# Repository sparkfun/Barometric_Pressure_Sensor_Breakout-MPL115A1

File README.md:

SparkFun Barometric Pressure Sensor Breakout - MPL115A1
========================================

[*SparkFun Barometric Pressure Sensor Breakout - MPL115A1 (SEN-09721)*](https://www.sparkfun.com/products/9721)

Now mounted on a breakout board, the MPL115A1 is a digital barometer that uses MEMs technology to give accurate pressure measurements between 50kPa and 115kPa.
We stock the SPI interface version of the sensor. 
Average current consumption is 10µA at one measurement per second.

Repository Contents
-------------------

* **/Firmware** - Example code 
* **/Hardware** - Eagle design files (.brd, .sch)
* **/Libraries** - Libraries for use with the <PRODUCT NAME>
* **/Production** - Production panel files (.brd)

Documentation
--------------
* **[SparkFun Fritzing repo](https://github.com/sparkfun/Fritzing_Parts)** - Fritzing diagrams for SparkFun products.
* **[SparkFun 3D Model repo](https://github.com/sparkfun/3D_Models)** - 3D models of SparkFun products. 

License Information
-------------------
This product is _**open source**_! 

The **hardware** is released under [Creative Commons ShareAlike 4.0 International](https://creativecommons.org/licenses/by-sa/4.0/).

The **code** is beerware; if you see me (or any other SparkFun employee) at the local, and you've found our code helpful, please buy us a round!

Please use, reuse, and modify these files as you see fit. Please maintain attribution to SparkFun Electronics and release anything derivative under the same license.

Distributed as-is; no warranty is given.

- Your friends at SparkFun.

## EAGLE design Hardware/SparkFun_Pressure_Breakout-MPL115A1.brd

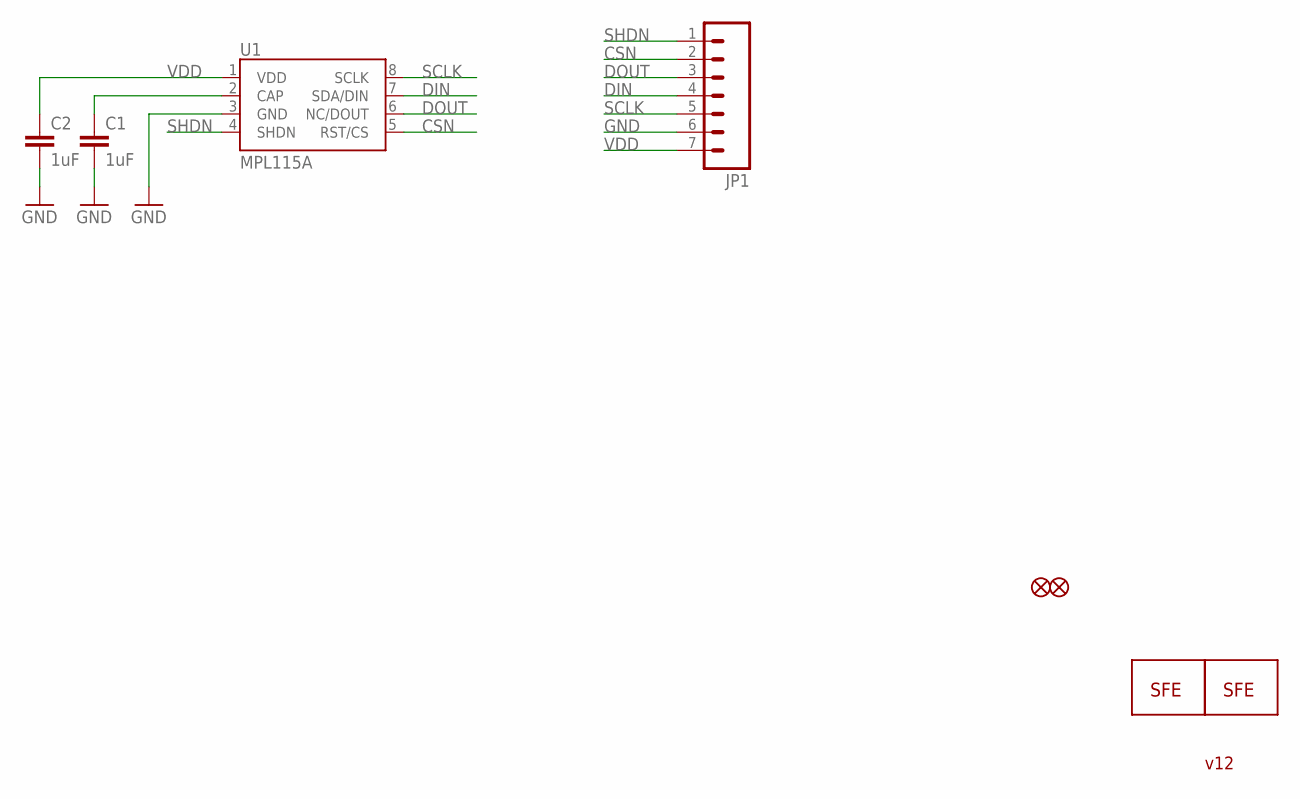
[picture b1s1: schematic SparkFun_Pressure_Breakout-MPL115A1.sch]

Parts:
C1, C2: 1uF; 0603-CAP
FID1, FID2: FIDUCIALUFIDUCIAL; MICRO-FIDUCIAL
JP1: M07; 1X07
JP2: LOGO-SFESK; SFE-LOGO-FLAME
JP3: LOGO-SFENW2; SFE-NEW-WEB
U1: MPL115A; LGA8

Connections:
CAP: C1.1, U1.2 (CAP)
CSN: JP1.2, U1.5 (RST/CS)
DIN: JP1.4, U1.7 (SDA/DIN)
DOUT: JP1.3, U1.6 (NC/DOUT)
GND: C1.2, C2.2, JP1.6, U1.3 (GND)
SCLK: JP1.5, U1.8 (SCLK)
SHDN: JP1.1, U1.4 (SHDN)
VDD: C2.1, JP1.7, U1.1 (VDD)

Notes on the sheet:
v12

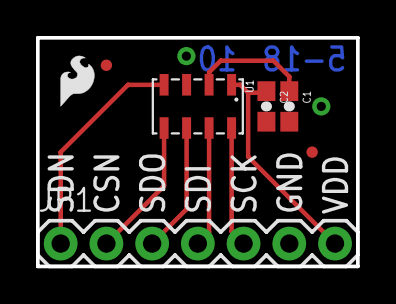
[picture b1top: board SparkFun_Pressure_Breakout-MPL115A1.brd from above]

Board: 2 copper layers, 17.8 x 12.7 mm, 8 parts (1 on the bottom side), 8 nets.

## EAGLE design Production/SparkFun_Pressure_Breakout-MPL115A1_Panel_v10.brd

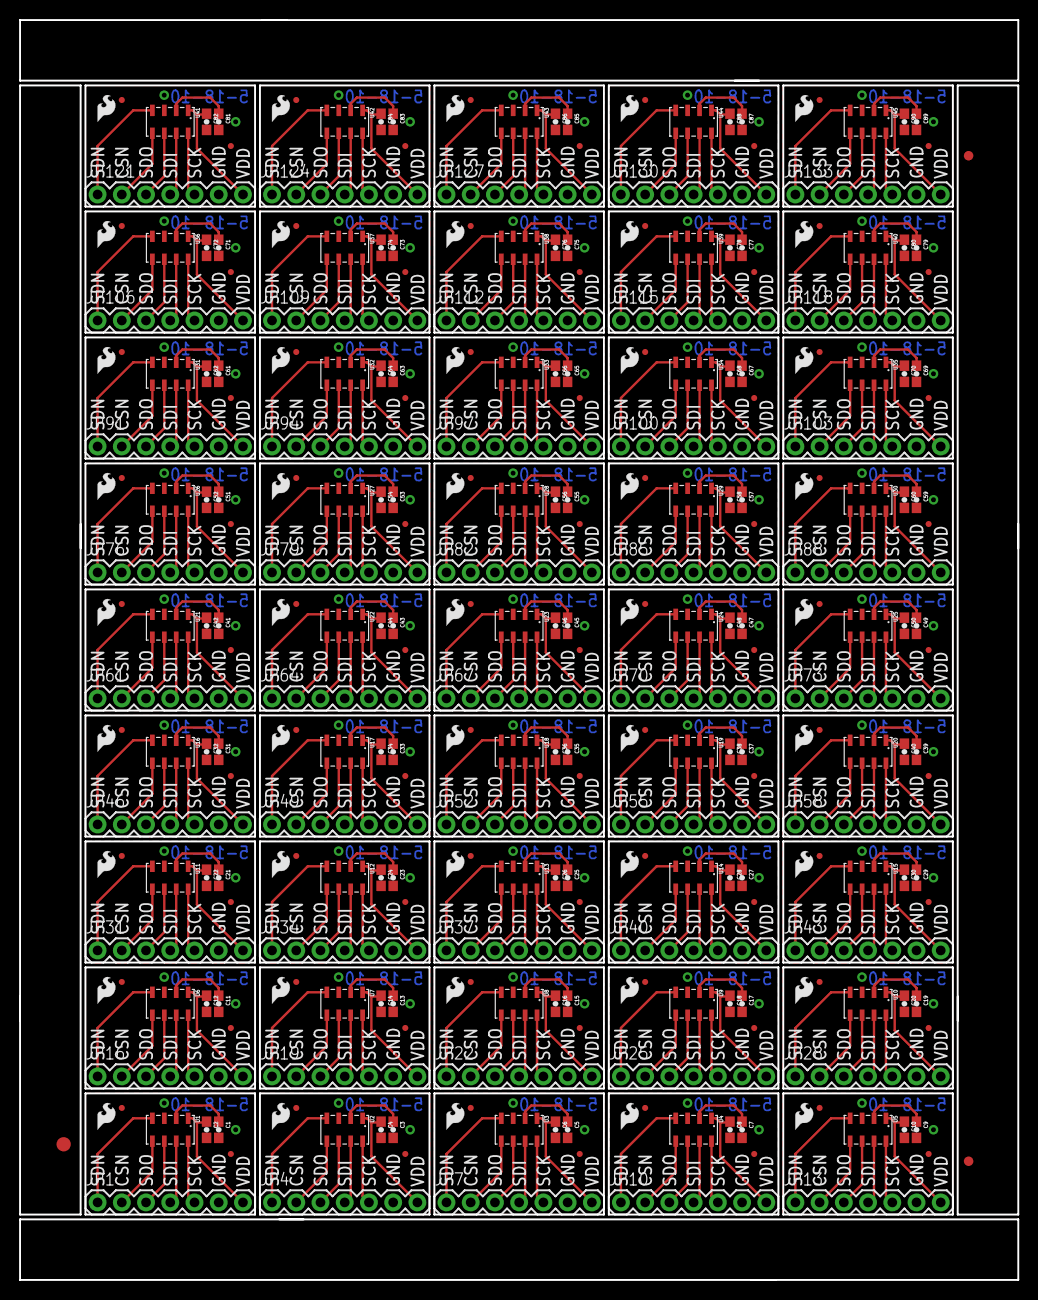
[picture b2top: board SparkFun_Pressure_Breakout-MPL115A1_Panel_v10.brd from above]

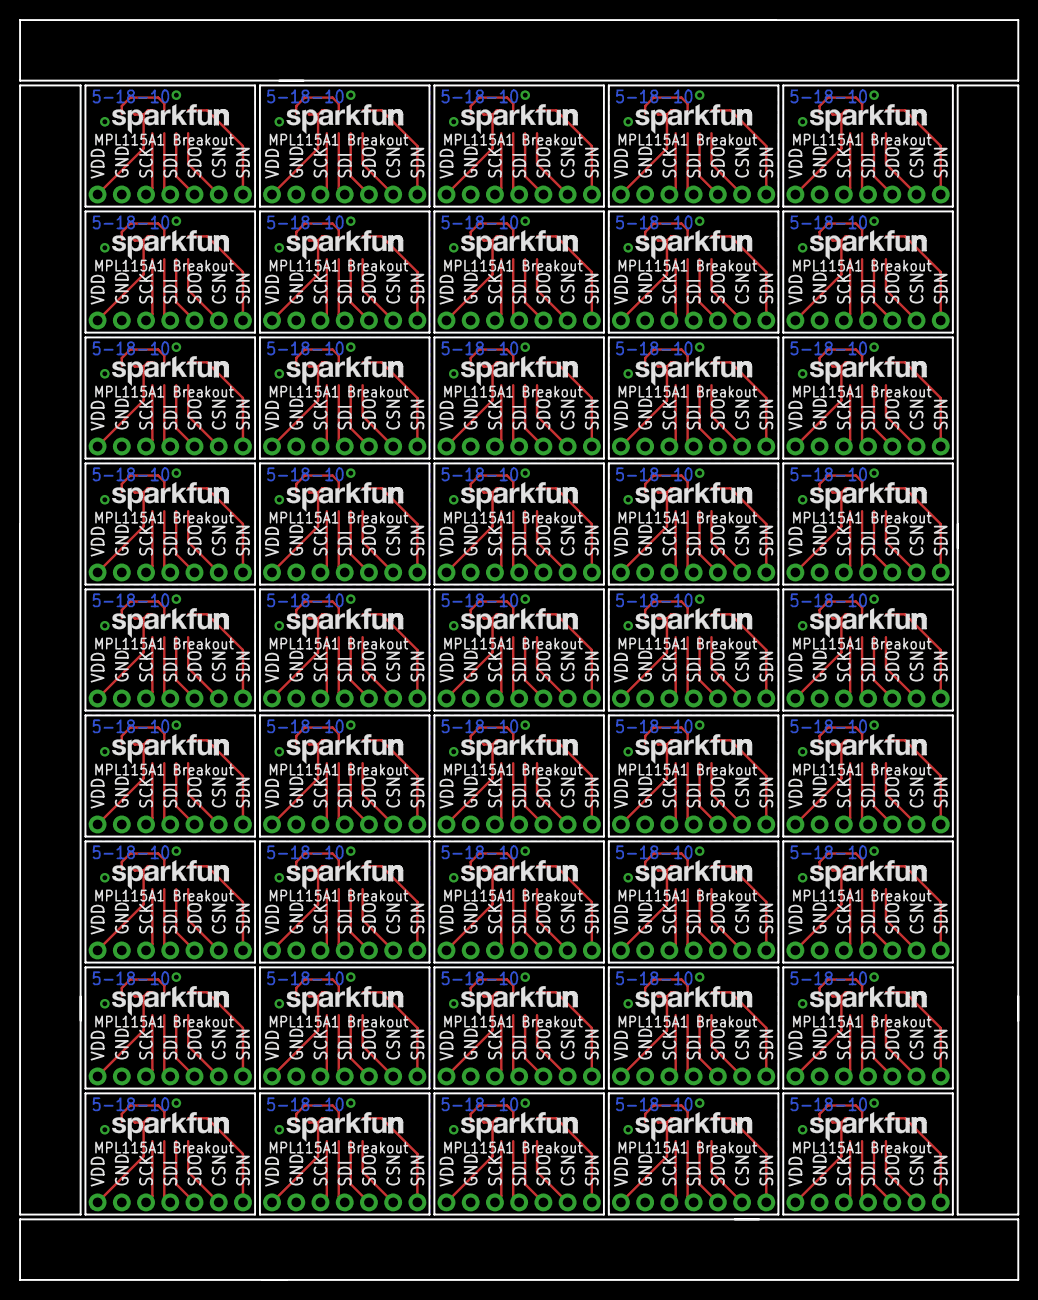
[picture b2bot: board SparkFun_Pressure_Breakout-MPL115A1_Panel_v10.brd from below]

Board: 2 copper layers, 104.6 x 132.1 mm, 363 parts (45 on the bottom side), 360 nets.

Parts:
C1, C2, C3, C4, C5, C6, C7, C8, C9, C10, C11, C12, C13, C14, C15, C16, C17, C18, C19, C20, C21, C22, C23, C24, C25, C26, C27, C28, C29, C30, C31, C32, C33, C34, C35, C36, C37, C38, C39, C40, C41, C42, C43, C44, C45, C46, C47, C48, C49, C50, C51, C52, C53, C54, C55, C56, C57, C58, C59, C60, C61, C62, C63, C64, C65, C66, C67, C68, C69, C70, C71, C72, C73, C74, C75, C76, C77, C78, C79, C80, C81, C82, C83, C84, C85, C86, C87, C88, C89, C90: 1uF; 0603-CAP
E$1: FIDUCIAL-1.5X3
E$5, E$6: FIDUCIAL-1X2
FID1, FID2, FID3, FID4, FID5, FID6, FID7, FID8, FID9, FID10, FID11, FID12, FID13, FID14, FID15, FID16, FID17, FID18, FID19, FID20, FID21, FID22, FID23, FID24, FID25, FID26, FID27, FID28, FID29, FID30, FID31, FID32, FID33, FID34, FID35, FID36, FID37, FID38, FID39, FID40, FID41, FID42, FID43, FID44, FID45, FID46, FID47, FID48, FID49, FID50, FID51, FID52, FID53, FID54, FID55, FID56, FID57, FID58, FID59, FID60, FID61, FID62, FID63, FID64, FID65, FID66, FID67, FID68, FID69, FID70, FID71, FID72, FID73, FID74, FID75, FID76, FID77, FID78, FID79, FID80, FID81, FID82, FID83, FID84, FID85, FID86, FID87, FID88, FID89, FID90: FIDUCIALUFIDUCIAL; MICRO-FIDUCIAL
JP1, JP4, JP7, JP10, JP13, JP16, JP19, JP22, JP25, JP28, JP31, JP34, JP37, JP40, JP43, JP46, JP49, JP52, JP55, JP58, JP61, JP64, JP67, JP70, JP73, JP76, JP79, JP82, JP85, JP88, JP91, JP94, JP97, JP100, JP103, JP106, JP109, JP112, JP115, JP118, JP121, JP124, JP127, JP130, JP133: 1X07
JP2, JP5, JP8, JP11, JP14, JP17, JP20, JP23, JP26, JP29, JP32, JP35, JP38, JP41, JP44, JP47, JP50, JP53, JP56, JP59, JP62, JP65, JP68, JP71, JP74, JP77, JP80, JP83, JP86, JP89, JP92, JP95, JP98, JP101, JP104, JP107, JP110, JP113, JP116, JP119, JP122, JP125, JP128, JP131, JP134: LOGO-SFESK; SFE-LOGO-FLAME
JP3, JP6, JP9, JP12, JP15, JP18, JP21, JP24, JP27, JP30, JP33, JP36, JP39, JP42, JP45, JP48, JP51, JP54, JP57, JP60, JP63, JP66, JP69, JP72, JP75, JP78, JP81, JP84, JP87, JP90, JP93, JP96, JP99, JP102, JP105, JP108, JP111, JP114, JP117, JP120, JP123, JP126, JP129, JP132, JP135: LOGO-SFENW2; SFE-NEW-WEB
U1, U2, U3, U4, U5, U6, U7, U8, U9, U10, U11, U12, U13, U14, U15, U16, U17, U18, U19, U20, U21, U22, U23, U24, U25, U26, U27, U28, U29, U30, U31, U32, U33, U34, U35, U36, U37, U38, U39, U40, U41, U42, U43, U44, U45: MPL115A; LGA8

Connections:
CAP: C1.1, U1.2
CAP1: C3.1, U2.2
CAP2: C5.1, U3.2
CAP3: C7.1, U4.2
CAP4: C9.1, U5.2
CAP5: C11.1, U6.2
CAP6: C13.1, U7.2
CAP7: C15.1, U8.2
CAP8: C17.1, U9.2
CAP9: C19.1, U10.2
CAP10: C21.1, U11.2
CAP11: C23.1, U12.2
CAP12: C25.1, U13.2
CAP13: C27.1, U14.2
CAP14: C29.1, U15.2
CAP15: C31.1, U16.2
CAP16: C33.1, U17.2
CAP17: C35.1, U18.2
CAP18: C37.1, U19.2
CAP19: C39.1, U20.2
CAP20: C41.1, U21.2
CAP21: C43.1, U22.2
CAP22: C45.1, U23.2
CAP23: C47.1, U24.2
CAP24: C49.1, U25.2
CAP25: C51.1, U26.2
CAP26: C53.1, U27.2
CAP27: C55.1, U28.2
CAP28: C57.1, U29.2
CAP29: C59.1, U30.2
CAP30: C61.1, U31.2
CAP31: C63.1, U32.2
CAP32: C65.1, U33.2
CAP33: C67.1, U34.2
CAP34: C69.1, U35.2
CAP35: C71.1, U36.2
CAP36: C73.1, U37.2
CAP37: C75.1, U38.2
CAP38: C77.1, U39.2
CAP39: C79.1, U40.2
CAP40: C81.1, U41.2
CAP41: C83.1, U42.2
CAP42: C85.1, U43.2
CAP43: C87.1, U44.2
CAP44: C89.1, U45.2
CSN: JP1.2, U1.5
CSN1: JP4.2, U2.5
CSN2: JP7.2, U3.5
CSN3: JP10.2, U4.5
CSN4: JP13.2, U5.5
CSN5: JP16.2, U6.5
CSN6: JP19.2, U7.5
CSN7: JP22.2, U8.5
CSN8: JP25.2, U9.5
CSN9: JP28.2, U10.5
CSN10: JP31.2, U11.5
CSN11: JP34.2, U12.5
CSN12: JP37.2, U13.5
CSN13: JP40.2, U14.5
CSN14: JP43.2, U15.5
CSN15: JP46.2, U16.5
CSN16: JP49.2, U17.5
CSN17: JP52.2, U18.5
CSN18: JP55.2, U19.5
CSN19: JP58.2, U20.5
CSN20: JP61.2, U21.5
CSN21: JP64.2, U22.5
CSN22: JP67.2, U23.5
CSN23: JP70.2, U24.5
CSN24: JP73.2, U25.5
CSN25: JP76.2, U26.5
CSN26: JP79.2, U27.5
CSN27: JP82.2, U28.5
CSN28: JP85.2, U29.5
CSN29: JP88.2, U30.5
CSN30: JP91.2, U31.5
CSN31: JP94.2, U32.5
CSN32: JP97.2, U33.5
CSN33: JP100.2, U34.5
CSN34: JP103.2, U35.5
CSN35: JP106.2, U36.5
CSN36: JP109.2, U37.5
CSN37: JP112.2, U38.5
CSN38: JP115.2, U39.5
CSN39: JP118.2, U40.5
CSN40: JP121.2, U41.5
CSN41: JP124.2, U42.5
CSN42: JP127.2, U43.5
CSN43: JP130.2, U44.5
CSN44: JP133.2, U45.5
DIN: JP1.4, U1.7
DIN1: JP4.4, U2.7
DIN2: JP7.4, U3.7
DIN3: JP10.4, U4.7
DIN4: JP13.4, U5.7
DIN5: JP16.4, U6.7
DIN6: JP19.4, U7.7
DIN7: JP22.4, U8.7
DIN8: JP25.4, U9.7
DIN9: JP28.4, U10.7
DIN10: JP31.4, U11.7
DIN11: JP34.4, U12.7
DIN12: JP37.4, U13.7
DIN13: JP40.4, U14.7
DIN14: JP43.4, U15.7
DIN15: JP46.4, U16.7
DIN16: JP49.4, U17.7
DIN17: JP52.4, U18.7
DIN18: JP55.4, U19.7
DIN19: JP58.4, U20.7
DIN20: JP61.4, U21.7
DIN21: JP64.4, U22.7
DIN22: JP67.4, U23.7
DIN23: JP70.4, U24.7
DIN24: JP73.4, U25.7
DIN25: JP76.4, U26.7
DIN26: JP79.4, U27.7
DIN27: JP82.4, U28.7
DIN28: JP85.4, U29.7
DIN29: JP88.4, U30.7
DIN30: JP91.4, U31.7
DIN31: JP94.4, U32.7
DIN32: JP97.4, U33.7
DIN33: JP100.4, U34.7
DIN34: JP103.4, U35.7
DIN35: JP106.4, U36.7
DIN36: JP109.4, U37.7
DIN37: JP112.4, U38.7
DIN38: JP115.4, U39.7
DIN39: JP118.4, U40.7
DIN40: JP121.4, U41.7
DIN41: JP124.4, U42.7
DIN42: JP127.4, U43.7
DIN43: JP130.4, U44.7
DIN44: JP133.4, U45.7
DOUT: JP1.3, U1.6
DOUT1: JP4.3, U2.6
DOUT2: JP7.3, U3.6
DOUT3: JP10.3, U4.6
DOUT4: JP13.3, U5.6
DOUT5: JP16.3, U6.6
DOUT6: JP19.3, U7.6
DOUT7: JP22.3, U8.6
DOUT8: JP25.3, U9.6
DOUT9: JP28.3, U10.6
DOUT10: JP31.3, U11.6
DOUT11: JP34.3, U12.6
DOUT12: JP37.3, U13.6
DOUT13: JP40.3, U14.6
DOUT14: JP43.3, U15.6
DOUT15: JP46.3, U16.6
DOUT16: JP49.3, U17.6
DOUT17: JP52.3, U18.6
DOUT18: JP55.3, U19.6
DOUT19: JP58.3, U20.6
DOUT20: JP61.3, U21.6
DOUT21: JP64.3, U22.6
DOUT22: JP67.3, U23.6
DOUT23: JP70.3, U24.6
DOUT24: JP73.3, U25.6
DOUT25: JP76.3, U26.6
DOUT26: JP79.3, U27.6
DOUT27: JP82.3, U28.6
DOUT28: JP85.3, U29.6
DOUT29: JP88.3, U30.6
DOUT30: JP91.3, U31.6
DOUT31: JP94.3, U32.6
DOUT32: JP97.3, U33.6
DOUT33: JP100.3, U34.6
DOUT34: JP103.3, U35.6
DOUT35: JP106.3, U36.6
DOUT36: JP109.3, U37.6
DOUT37: JP112.3, U38.6
DOUT38: JP115.3, U39.6
DOUT39: JP118.3, U40.6
DOUT40: JP121.3, U41.6
DOUT41: JP124.3, U42.6
DOUT42: JP127.3, U43.6
DOUT43: JP130.3, U44.6
DOUT44: JP133.3, U45.6
GND: C1.2, C2.2, JP1.6, U1.3
GND1: C3.2, C4.2, JP4.6, U2.3
GND2: C5.2, C6.2, JP7.6, U3.3
GND3: C7.2, C8.2, JP10.6, U4.3
GND4: C9.2, C10.2, JP13.6, U5.3
GND5: C11.2, C12.2, JP16.6, U6.3
GND6: C13.2, C14.2, JP19.6, U7.3
GND7: C15.2, C16.2, JP22.6, U8.3
GND8: C17.2, C18.2, JP25.6, U9.3
GND9: C19.2, C20.2, JP28.6, U10.3
GND10: C21.2, C22.2, JP31.6, U11.3
GND11: C23.2, C24.2, JP34.6, U12.3
GND12: C25.2, C26.2, JP37.6, U13.3
GND13: C27.2, C28.2, JP40.6, U14.3
GND14: C29.2, C30.2, JP43.6, U15.3
GND15: C31.2, C32.2, JP46.6, U16.3
GND16: C33.2, C34.2, JP49.6, U17.3
GND17: C35.2, C36.2, JP52.6, U18.3
GND18: C37.2, C38.2, JP55.6, U19.3
GND19: C39.2, C40.2, JP58.6, U20.3
GND20: C41.2, C42.2, JP61.6, U21.3
GND21: C43.2, C44.2, JP64.6, U22.3
GND22: C45.2, C46.2, JP67.6, U23.3
GND23: C47.2, C48.2, JP70.6, U24.3
GND24: C49.2, C50.2, JP73.6, U25.3
GND25: C51.2, C52.2, JP76.6, U26.3
GND26: C53.2, C54.2, JP79.6, U27.3
GND27: C55.2, C56.2, JP82.6, U28.3
GND28: C57.2, C58.2, JP85.6, U29.3
GND29: C59.2, C60.2, JP88.6, U30.3
GND30: C61.2, C62.2, JP91.6, U31.3
GND31: C63.2, C64.2, JP94.6, U32.3
GND32: C65.2, C66.2, JP97.6, U33.3
GND33: C67.2, C68.2, JP100.6, U34.3
GND34: C69.2, C70.2, JP103.6, U35.3
GND35: C71.2, C72.2, JP106.6, U36.3
GND36: C73.2, C74.2, JP109.6, U37.3
GND37: C75.2, C76.2, JP112.6, U38.3
GND38: C77.2, C78.2, JP115.6, U39.3
GND39: C79.2, C80.2, JP118.6, U40.3
GND40: C81.2, C82.2, JP121.6, U41.3
GND41: C83.2, C84.2, JP124.6, U42.3
GND42: C85.2, C86.2, JP127.6, U43.3
GND43: C87.2, C88.2, JP130.6, U44.3
GND44: C89.2, C90.2, JP133.6, U45.3
SCLK: JP1.5, U1.8
SCLK1: JP4.5, U2.8
SCLK2: JP7.5, U3.8
SCLK3: JP10.5, U4.8
SCLK4: JP13.5, U5.8
SCLK5: JP16.5, U6.8
SCLK6: JP19.5, U7.8
SCLK7: JP22.5, U8.8
SCLK8: JP25.5, U9.8
SCLK9: JP28.5, U10.8
SCLK10: JP31.5, U11.8
SCLK11: JP34.5, U12.8
SCLK12: JP37.5, U13.8
SCLK13: JP40.5, U14.8
SCLK14: JP43.5, U15.8
SCLK15: JP46.5, U16.8
SCLK16: JP49.5, U17.8
SCLK17: JP52.5, U18.8
SCLK18: JP55.5, U19.8
SCLK19: JP58.5, U20.8
SCLK20: JP61.5, U21.8
SCLK21: JP64.5, U22.8
SCLK22: JP67.5, U23.8
SCLK23: JP70.5, U24.8
SCLK24: JP73.5, U25.8
SCLK25: JP76.5, U26.8
SCLK26: JP79.5, U27.8
SCLK27: JP82.5, U28.8
SCLK28: JP85.5, U29.8
SCLK29: JP88.5, U30.8
SCLK30: JP91.5, U31.8
SCLK31: JP94.5, U32.8
SCLK32: JP97.5, U33.8
SCLK33: JP100.5, U34.8
SCLK34: JP103.5, U35.8
SCLK35: JP106.5, U36.8
SCLK36: JP109.5, U37.8
SCLK37: JP112.5, U38.8
SCLK38: JP115.5, U39.8
SCLK39: JP118.5, U40.8
SCLK40: JP121.5, U41.8
SCLK41: JP124.5, U42.8
SCLK42: JP127.5, U43.8
SCLK43: JP130.5, U44.8
SCLK44: JP133.5, U45.8
SHDN: JP1.1, U1.4
SHDN1: JP4.1, U2.4
SHDN2: JP7.1, U3.4
SHDN3: JP10.1, U4.4
SHDN4: JP13.1, U5.4
SHDN5: JP16.1, U6.4
SHDN6: JP19.1, U7.4
SHDN7: JP22.1, U8.4
SHDN8: JP25.1, U9.4
SHDN9: JP28.1, U10.4
SHDN10: JP31.1, U11.4
SHDN11: JP34.1, U12.4
SHDN12: JP37.1, U13.4
SHDN13: JP40.1, U14.4
SHDN14: JP43.1, U15.4
SHDN15: JP46.1, U16.4
SHDN16: JP49.1, U17.4
SHDN17: JP52.1, U18.4
SHDN18: JP55.1, U19.4
SHDN19: JP58.1, U20.4
SHDN20: JP61.1, U21.4
SHDN21: JP64.1, U22.4
SHDN22: JP67.1, U23.4
SHDN23: JP70.1, U24.4
SHDN24: JP73.1, U25.4
SHDN25: JP76.1, U26.4
SHDN26: JP79.1, U27.4
SHDN27: JP82.1, U28.4
SHDN28: JP85.1, U29.4
SHDN29: JP88.1, U30.4
SHDN30: JP91.1, U31.4
SHDN31: JP94.1, U32.4
SHDN32: JP97.1, U33.4
SHDN33: JP100.1, U34.4
SHDN34: JP103.1, U35.4
SHDN35: JP106.1, U36.4
SHDN36: JP109.1, U37.4
SHDN37: JP112.1, U38.4
SHDN38: JP115.1, U39.4
SHDN39: JP118.1, U40.4
SHDN40: JP121.1, U41.4
SHDN41: JP124.1, U42.4
SHDN42: JP127.1, U43.4
SHDN43: JP130.1, U44.4
SHDN44: JP133.1, U45.4
VDD: C2.1, JP1.7, U1.1
VDD1: C4.1, JP4.7, U2.1
VDD2: C6.1, JP7.7, U3.1
VDD3: C8.1, JP10.7, U4.1
VDD4: C10.1, JP13.7, U5.1
VDD5: C12.1, JP16.7, U6.1
VDD6: C14.1, JP19.7, U7.1
VDD7: C16.1, JP22.7, U8.1
VDD8: C18.1, JP25.7, U9.1
VDD9: C20.1, JP28.7, U10.1
VDD10: C22.1, JP31.7, U11.1
VDD11: C24.1, JP34.7, U12.1
VDD12: C26.1, JP37.7, U13.1
VDD13: C28.1, JP40.7, U14.1
VDD14: C30.1, JP43.7, U15.1
VDD15: C32.1, JP46.7, U16.1
VDD16: C34.1, JP49.7, U17.1
VDD17: C36.1, JP52.7, U18.1
VDD18: C38.1, JP55.7, U19.1
VDD19: C40.1, JP58.7, U20.1
VDD20: C42.1, JP61.7, U21.1
VDD21: C44.1, JP64.7, U22.1
VDD22: C46.1, JP67.7, U23.1
VDD23: C48.1, JP70.7, U24.1
VDD24: C50.1, JP73.7, U25.1
VDD25: C52.1, JP76.7, U26.1
VDD26: C54.1, JP79.7, U27.1
VDD27: C56.1, JP82.7, U28.1
VDD28: C58.1, JP85.7, U29.1
VDD29: C60.1, JP88.7, U30.1
VDD30: C62.1, JP91.7, U31.1
VDD31: C64.1, JP94.7, U32.1
VDD32: C66.1, JP97.7, U33.1
VDD33: C68.1, JP100.7, U34.1
VDD34: C70.1, JP103.7, U35.1
VDD35: C72.1, JP106.7, U36.1
VDD36: C74.1, JP109.7, U37.1
VDD37: C76.1, JP112.7, U38.1
VDD38: C78.1, JP115.7, U39.1
VDD39: C80.1, JP118.7, U40.1
VDD40: C82.1, JP121.7, U41.1
VDD41: C84.1, JP124.7, U42.1
VDD42: C86.1, JP127.7, U43.1
VDD43: C88.1, JP130.7, U44.1
VDD44: C90.1, JP133.7, U45.1

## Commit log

2015-05-06 Adding hardware files, example code
2015-11-18 added fids
2015-11-18 created new panel

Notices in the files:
parts and their libraries:
SparkFun-Aesthetics: Licensing: Creative Commons ShareAlike 4.0 International - https://creativecommons.org/licenses/by-sa/4.0
